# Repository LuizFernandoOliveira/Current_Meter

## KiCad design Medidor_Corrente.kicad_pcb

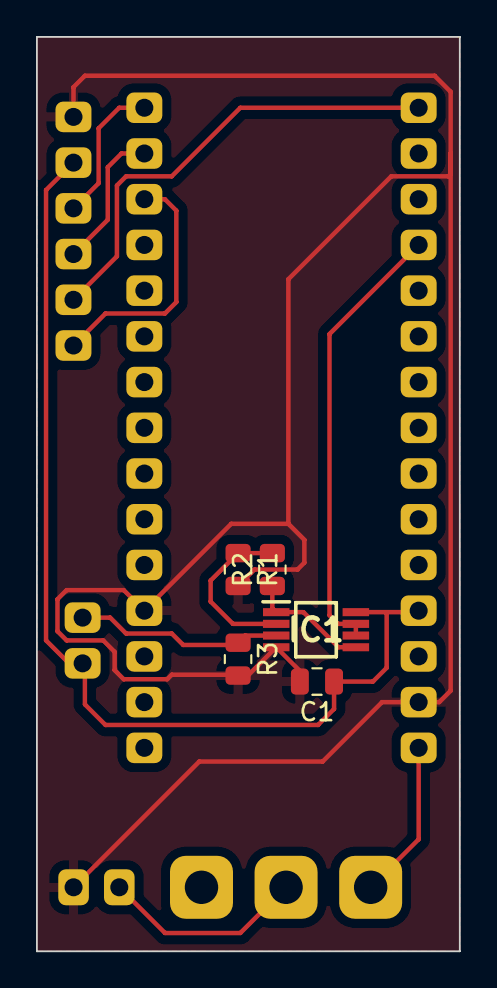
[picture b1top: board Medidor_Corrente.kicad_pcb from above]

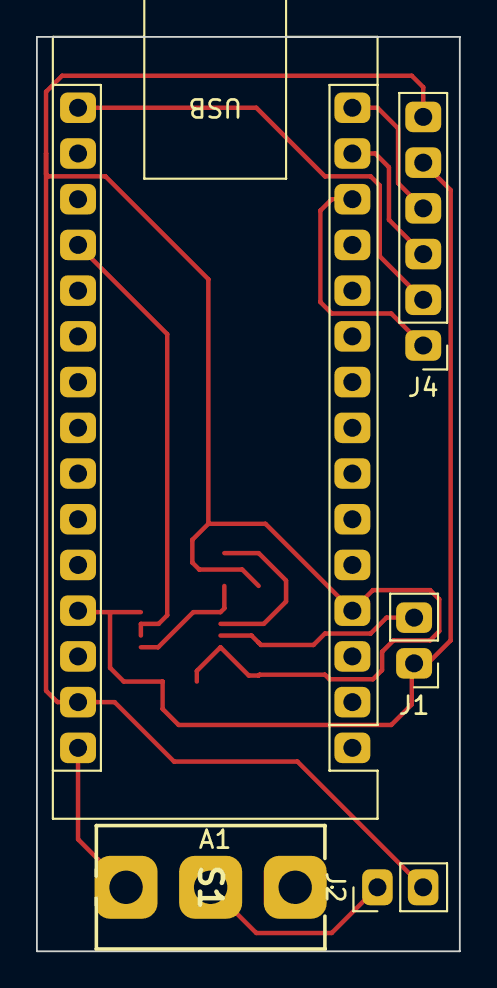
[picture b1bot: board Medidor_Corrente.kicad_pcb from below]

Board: 2 copper layers, 23.5 x 50.8 mm, 10 parts (5 on the bottom side), 12 nets.

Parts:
A1: Arduino_Nano_v3.x; Arduino_Nano
C1: 100nF; C_0805_2012Metric
IC1: TSZ122IYST; SOP65P490X110-8N
J1: Load; PinHeader_1x02_P2.54mm_Vertical
J2: Power; PinHeader_1x02_P2.54mm_Vertical
J4: SD Card; PinHeader_1x06_P2.54mm_Vertical
R1: 100 k; R_0805_2012Metric
R2: 10M; R_0805_2012Metric
R3: 1; R_0805_2012Metric
S1: A107SYCQ04

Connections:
+5V: A1.27 (+5V), C1.1, IC1.8 (VCC+), J1.1, J4.5
CS: A1.13 (D10), J4.1
GND: A1.4 (GND), A1.29 (GND), C1.2, IC1.4 (VCC-), J2.2, J4.6, R1.2, R3.2
I1: A1.19 (A0), IC1.6 (IN2-), IC1.7 (OUT2)
IN1: IC1.3 (IN1+), J1.2, R3.1
MISO: A1.15 (D12), J4.4
MOSI: A1.14 (D11), J4.3
unnamed: A1.30 (VIN), S1.3 (NO)
unnamed: IC1.2 (IN1-), R1.1, R2.2
unnamed: J2.1, S1.2 (COM)
OUT1: IC1.1 (OUT1), IC1.5 (IN2+), R2.1
SCK: A1.16 (D13), J4.2
